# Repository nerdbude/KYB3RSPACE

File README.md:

# KYB3RSPACE
OPENSOURCE HARD- AND SOFTWARE FOR NETRUNNER, HACKER AND NERDS

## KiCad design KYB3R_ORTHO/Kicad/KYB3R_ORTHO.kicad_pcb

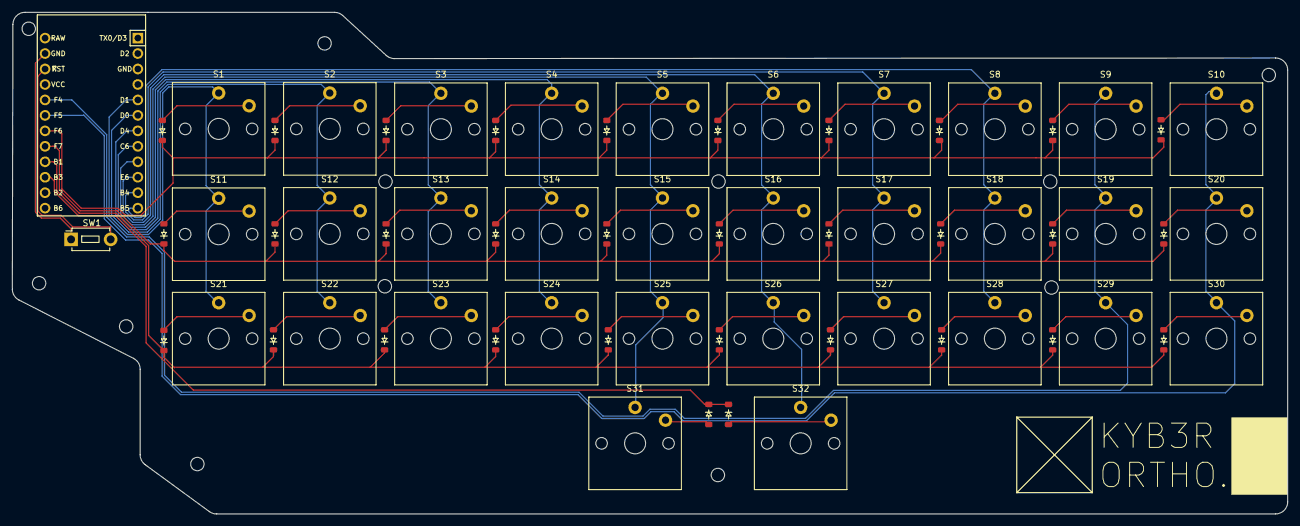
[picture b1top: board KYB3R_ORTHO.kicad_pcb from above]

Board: 2 copper layers, 209.5 x 82.4 mm, 66 parts (1 on the bottom side), 48 nets.

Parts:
D1, D2, D3, D4, D5, D6, D7, D8, D9, D10, D11, D12, D13, D14, D15, D16, D17, D18, D19, D20, D21, D22, D23, D24, D25, D26, D27, D28, D29, D30, D31, D32: Diode; Diode_SOD-123
S1, S2, S3, S4, S5, S6, S7, S8, S9, S10, S11, S12, S13, S14, S15, S16, S17, S18, S19, S20, S21, S22, S23, S24, S25, S26, S27, S28, S29, S30: Keyswitch; Choc_V1_1.00u
S31, S32: Keyswitch; Choc_V1_1.50u
SW1: SW_Push; Button_MJTP1250
U1: Arduino_Pro_Micro

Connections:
Column 0: S1.1, S11.1, S21.1, U1.5 (2/PD1)
Column 1: S2.1, S12.1, S22.1, U1.6 (3/PD0)
Column 2: S3.1, S13.1, S23.1, U1.7 (4/PD4)
Column 3: S4.1, S14.1, S24.1, U1.8 (5/PC6)
Column 4: S5.1, S15.1, S25.1, S31.1, U1.9 (6/PD7)
Column 5: S6.1, S16.1, S26.1, S32.1, U1.10 (7/PE6)
Column 6: S7.1, S17.1, S27.1, U1.11 (8/PB4)
Column 7: S8.1, S18.1, S28.1, U1.12 (9/PB5)
Column 8: S9.1, S19.1, S29.1, U1.20 (A3/PF4)
Column 9: S10.1, S20.1, S30.1, U1.19 (A2/PF5)
GND: SW1.1, U1.23 (GND)
unnamed: D1.2 (A), S1.2
unnamed: D2.2 (A), S2.2
unnamed: D3.2 (A), S11.2
unnamed: D4.2 (A), S12.2
unnamed: D5.2 (A), S21.2
unnamed: D6.2 (A), S22.2
unnamed: D7.2 (A), S3.2
unnamed: D8.2 (A), S13.2
unnamed: D9.2 (A), S23.2
unnamed: D10.2 (A), S4.2
unnamed: D11.2 (A), S14.2
unnamed: D12.2 (A), S24.2
unnamed: D13.2 (A), S5.2
unnamed: D14.2 (A), S15.2
unnamed: D15.2 (A), S25.2
unnamed: D16.2 (A), S6.2
unnamed: D17.2 (A), S16.2
unnamed: D18.2 (A), S26.2
unnamed: D19.2 (A), S7.2
unnamed: D20.2 (A), S8.2
unnamed: D21.2 (A), S9.2
unnamed: D22.2 (A), S10.2
unnamed: D23.2 (A), S17.2
unnamed: D24.2 (A), S18.2
unnamed: D25.2 (A), S19.2
unnamed: D26.2 (A), S20.2
unnamed: D27.2 (A), S30.2
unnamed: D28.2 (A), S29.2
unnamed: D29.2 (A), S28.2
unnamed: D30.2 (A), S27.2
unnamed: D31.2 (A), S31.2
unnamed: D32.2 (A), S32.2
RST: SW1.2, U1.22 (RST)
Row 0: D1.1 (K), D2.1 (K), D7.1 (K), D10.1 (K), D13.1 (K), D16.1 (K), D19.1 (K), D20.1 (K), D21.1 (K), D22.1 (K), U1.18 (A1/PF6)
Row 1: D3.1 (K), D4.1 (K), D8.1 (K), D11.1 (K), D14.1 (K), D17.1 (K), D23.1 (K), D24.1 (K), D25.1 (K), D26.1 (K), U1.17 (A0/PF7)
Row 2: D5.1 (K), D6.1 (K), D9.1 (K), D12.1 (K), D15.1 (K), D18.1 (K), D27.1 (K), D28.1 (K), D29.1 (K), D30.1 (K), U1.16 (15/PB1)
Row 3: D31.1 (K), D32.1 (K), U1.15 (14/PB3)

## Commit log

2025-05-06 commit the KYB3R.ORTHO files
2025-05-06 remove unused files
2025-05-06 typos
2025-05-25 adding licence
2025-05-25 adding kicad files
2025-05-27 make the switchholes smaller in plate
2025-05-27 make the switchholes smaller
